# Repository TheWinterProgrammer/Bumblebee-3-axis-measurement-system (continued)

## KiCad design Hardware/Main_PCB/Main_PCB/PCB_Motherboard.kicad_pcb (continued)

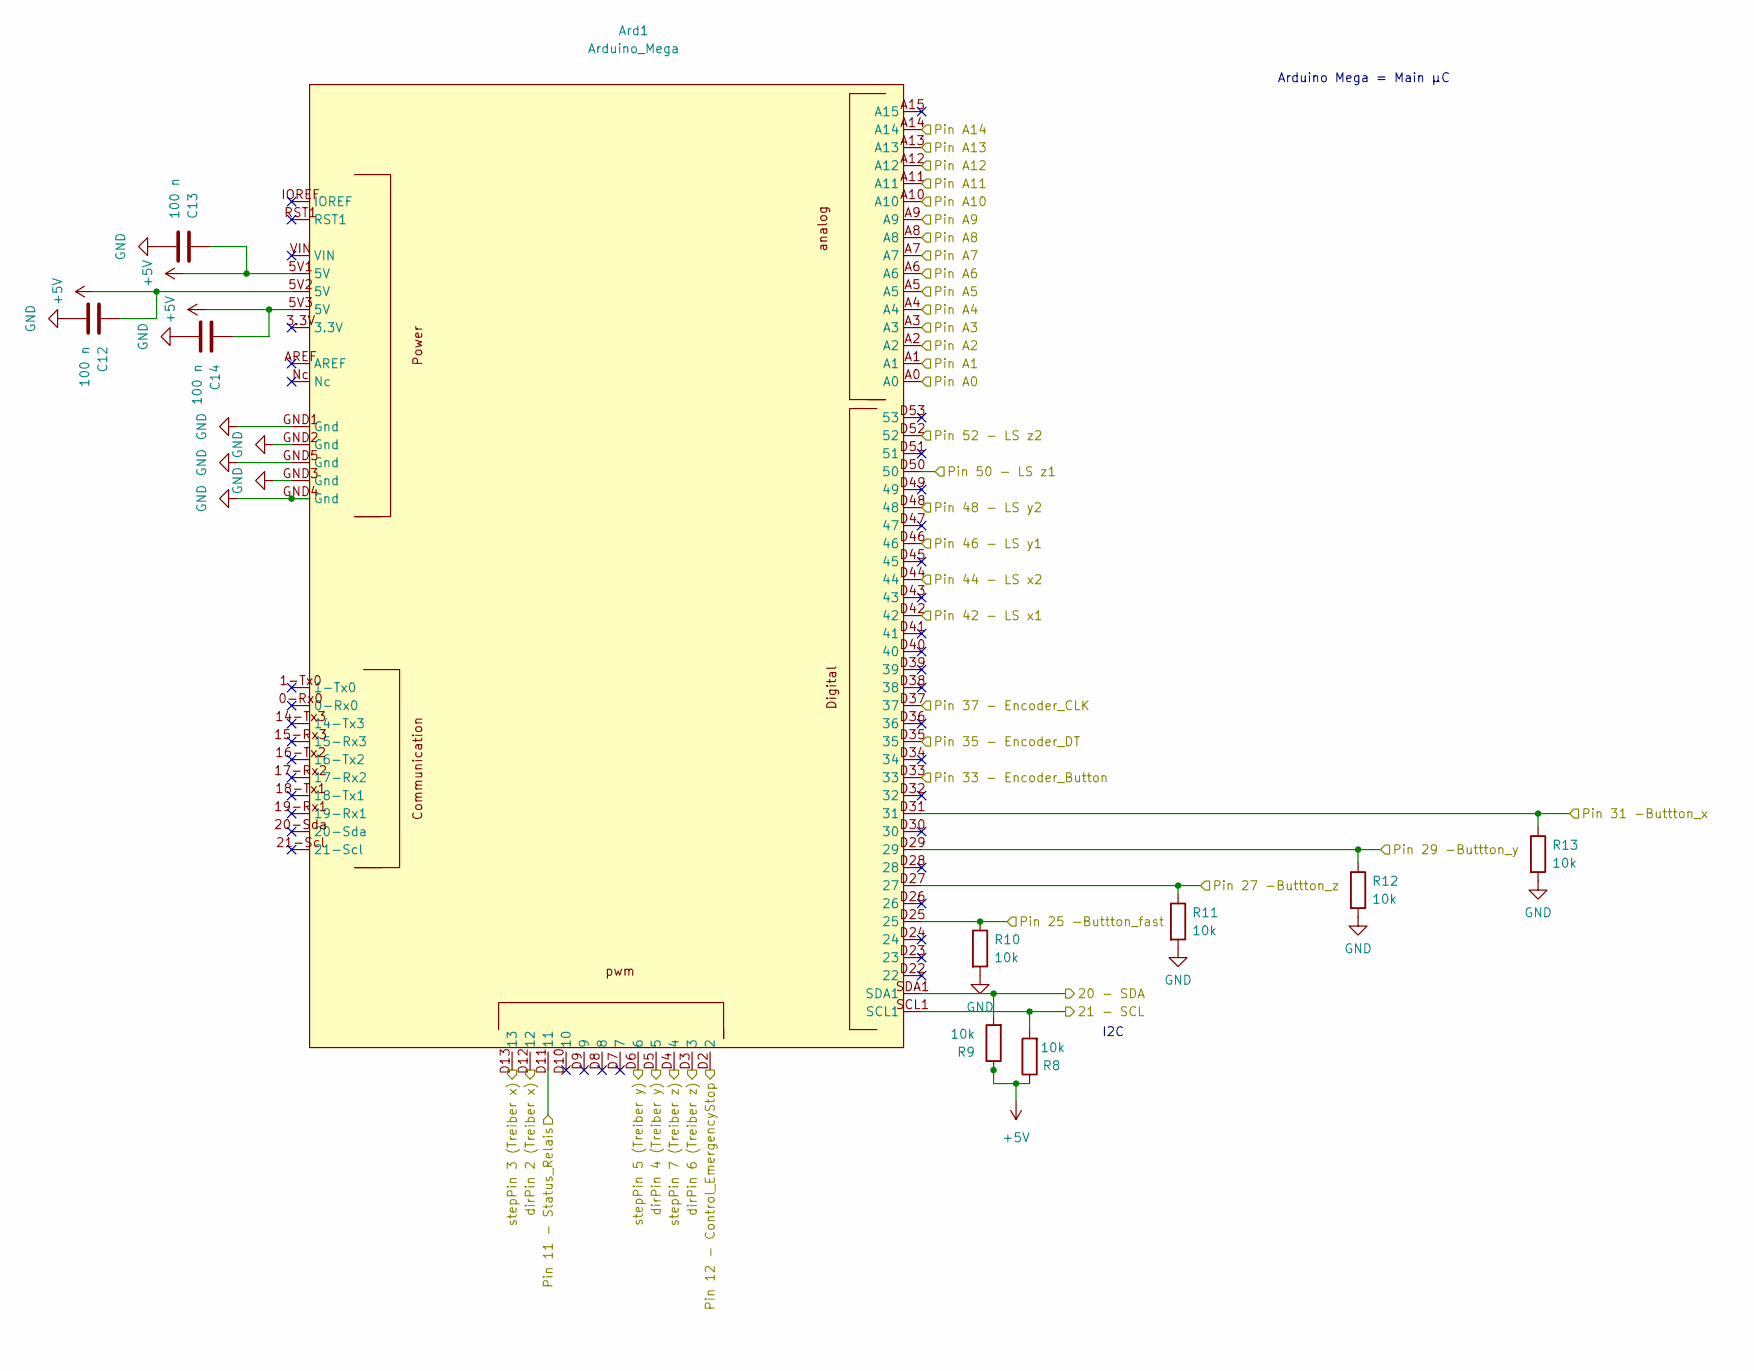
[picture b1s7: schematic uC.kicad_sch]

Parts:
Ard1: Arduino_Mega; Arduino-Mega
C12, C13, C14: 100 n; C_1206_3216Metric_Pad1.33x1.80mm_HandSolder
R8, R9, R10, R11, R12, R13: 10k; R_1206_3216Metric_Pad1.30x1.75mm_HandSolder

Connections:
+5V: Ard1.5V1 (5V), Ard1.5V2 (5V), Ard1.5V3 (5V), C12.1, C13.1, C14.1, R8.1, R9.1; also elsewhere on the board
/Connectors/Button-Encoder: Ard1.D33 (33); also elsewhere on the board
/Connectors/Button_fast: Ard1.D25 (25), R10.1; also elsewhere on the board
/Connectors/Button_x: Ard1.D31 (31), R13.1; also elsewhere on the board
/Connectors/Button_y: Ard1.D29 (29), R12.1; also elsewhere on the board
/Connectors/Button_z: Ard1.D27 (27), R11.1; also elsewhere on the board
/Connectors/CLK-Encoder: Ard1.D37 (37); also elsewhere on the board
/Connectors/DIR Treiber x: Ard1.D12 (12); also elsewhere on the board
/Connectors/DIR Treiber y: Ard1.D5 (5); also elsewhere on the board
/Connectors/DIR Treiber z: Ard1.D3 (3); also elsewhere on the board
/Connectors/DT-Encoder: Ard1.D35 (35); also elsewhere on the board
/Connectors/PUL Treiber x: Ard1.D13 (13); also elsewhere on the board
/Connectors/PUL Treiber y: Ard1.D6 (6); also elsewhere on the board
/Connectors/PUL Treiber z: Ard1.D4 (4); also elsewhere on the board
/Connectors/SCL_Display: Ard1.SCL1, R8.2; also elsewhere on the board
/Connectors/SDA_Display: Ard1.SDA1, R9.2; also elsewhere on the board
/Over Voltage Protection/µC-A3: Ard1.A3; also elsewhere on the board
/Over Voltage Protection/µC-A4: Ard1.A4; also elsewhere on the board
/Over Voltage Protection/µC-A5: Ard1.A5; also elsewhere on the board
/Over Voltage Protection/µC-A6: Ard1.A6; also elsewhere on the board
/Over Voltage Protection/µC-A7: Ard1.A7; also elsewhere on the board
/Over Voltage Protection/µC-A8: Ard1.A8; also elsewhere on the board
/Over Voltage Protection/µC-A9: Ard1.A9; also elsewhere on the board
/Over Voltage Protection/µC-A10: Ard1.A10; also elsewhere on the board
/Over Voltage Protection/µC-A11: Ard1.A11; also elsewhere on the board
/Over Voltage Protection/µC-A12: Ard1.A12; also elsewhere on the board
/Over Voltage Protection/µC-A13: Ard1.A13; also elsewhere on the board
/Over Voltage Protection/µC-A14: Ard1.A14; also elsewhere on the board
/PowerElectronic/Control_EmergencyStop: Ard1.D2 (2); also elsewhere on the board
/PowerElectronic/Status_Relais: Ard1.D11 (11); also elsewhere on the board
/PowerElectronic/U Driver x: Ard1.A0; also elsewhere on the board
/PowerElectronic/U Driver y: Ard1.A1; also elsewhere on the board
/PowerElectronic/U Driver z: Ard1.A2; also elsewhere on the board
/Voltage Converter/Signal LS x1 n. SW: Ard1.D42 (42); also elsewhere on the board
/Voltage Converter/Signal LS x2 n. SW: Ard1.D44 (44); also elsewhere on the board
/Voltage Converter/Signal LS y1 n. SW: Ard1.D46 (46); also elsewhere on the board
/Voltage Converter/Signal LS y2 n. SW: Ard1.D48 (48); also elsewhere on the board
/Voltage Converter/Signal LS z1 n. SW: Ard1.D50 (50); also elsewhere on the board
/Voltage Converter/Signal LS z2 n. SW: Ard1.D52 (52); also elsewhere on the board
GND: Ard1.GND1 (Gnd), Ard1.GND2 (Gnd), Ard1.GND3 (Gnd), Ard1.GND4 (Gnd), Ard1.GND5 (Gnd), C12.2, C13.2, C14.2, R10.2, R11.2, R12.2, R13.2; also elsewhere on the board

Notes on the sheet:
Arduino Mega = Main µC
I2C

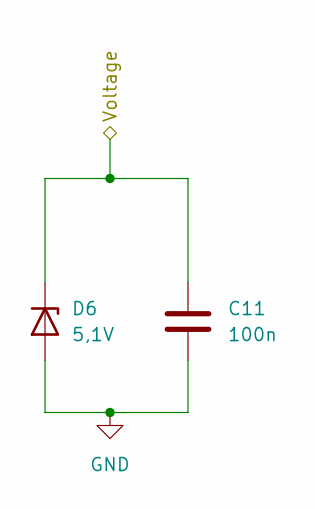
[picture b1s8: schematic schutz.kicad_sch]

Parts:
C11: 100n; C_1206_3216Metric_Pad1.33x1.80mm_HandSolder
D6: 5,1V; D_SMA_Handsoldering

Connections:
/PowerElectronic/Status_Relais: C11.1, D6.1 (K); also elsewhere on the board
GND: C11.2, D6.2 (A); also elsewhere on the board

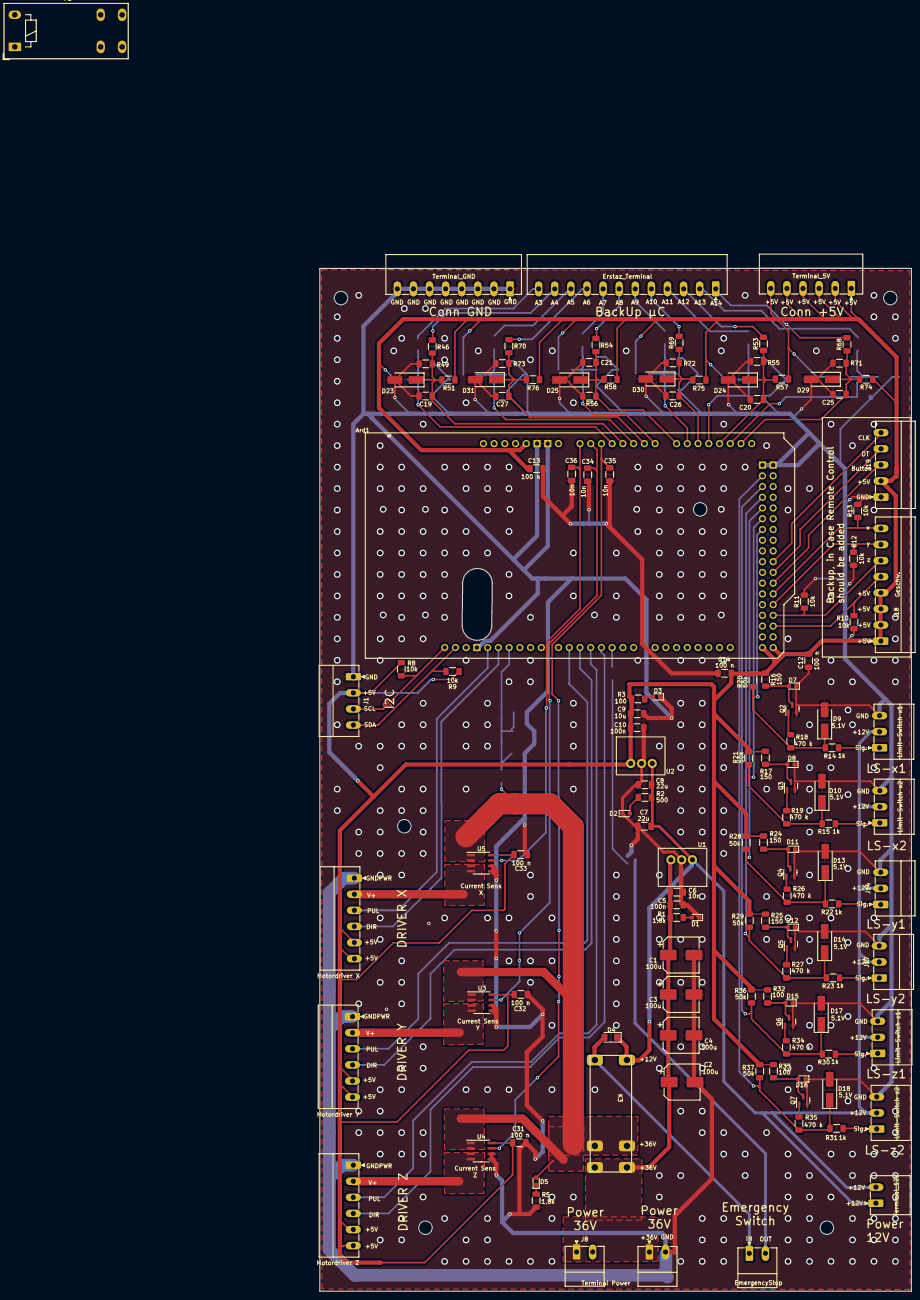
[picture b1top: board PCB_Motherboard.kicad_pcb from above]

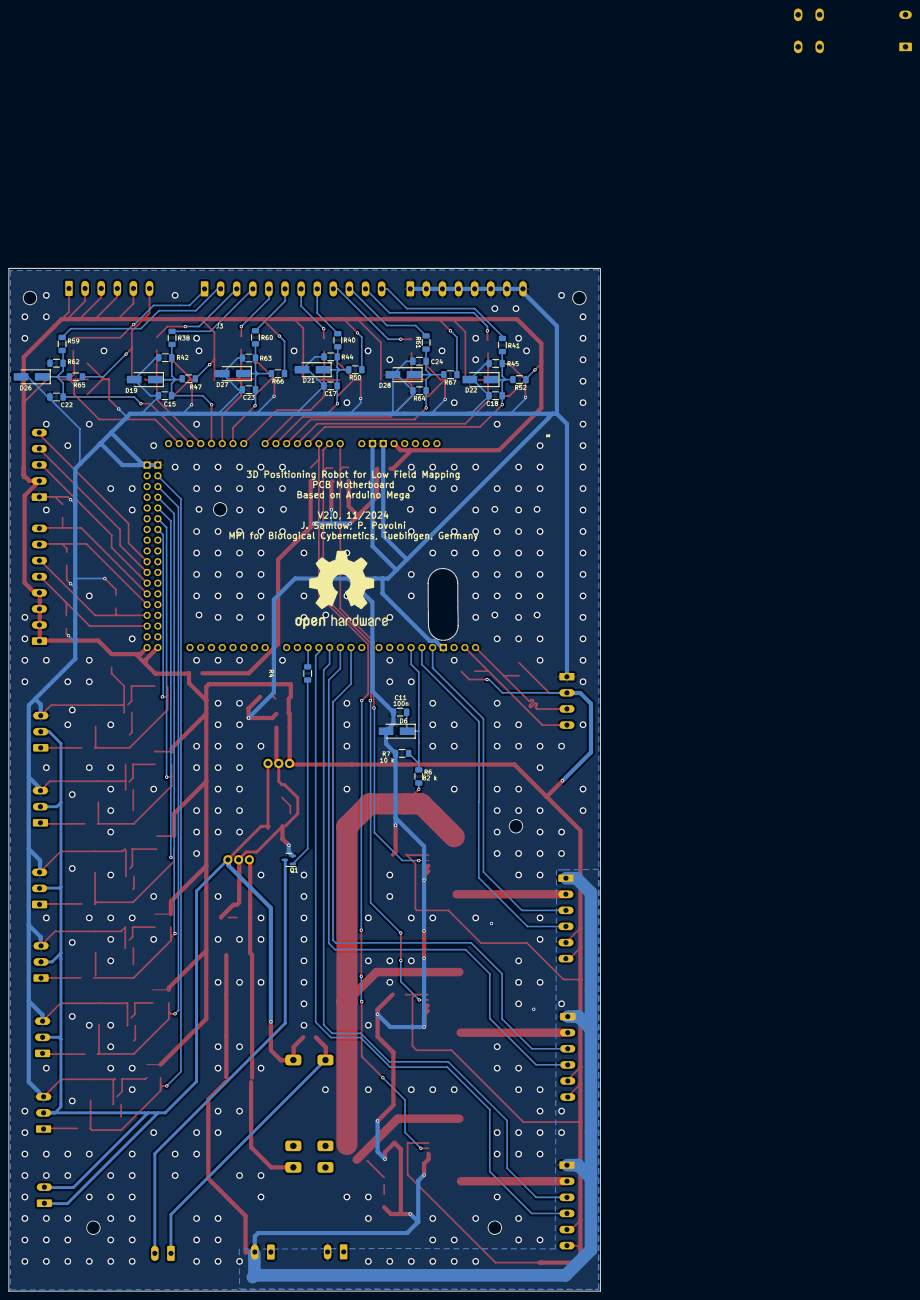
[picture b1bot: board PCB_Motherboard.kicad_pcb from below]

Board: 2 copper layers, 140.0 x 242.0 mm, 175 parts (37 on the bottom side), 83 nets.

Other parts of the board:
 : MountingHole_3.2mm_M3_DIN965
 #2,  #3,  #4,  #5,  #6: MountingHole_3.2mm_M3_DIN965
K1: PR22-12V-400-1A; Relay_SPST_Schrack-RT1-16A-FormA_RM5mm

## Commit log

2024-11-21 Version 1.0
